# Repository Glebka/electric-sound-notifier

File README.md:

# Electric Sound Notifier

Device designed to be connected to an AC-DC USB charger adapter. Upon plugging in, it emits three beeps to signal the presence of mains voltage. When the mains voltage is no longer detected it produces a prolonged beep.

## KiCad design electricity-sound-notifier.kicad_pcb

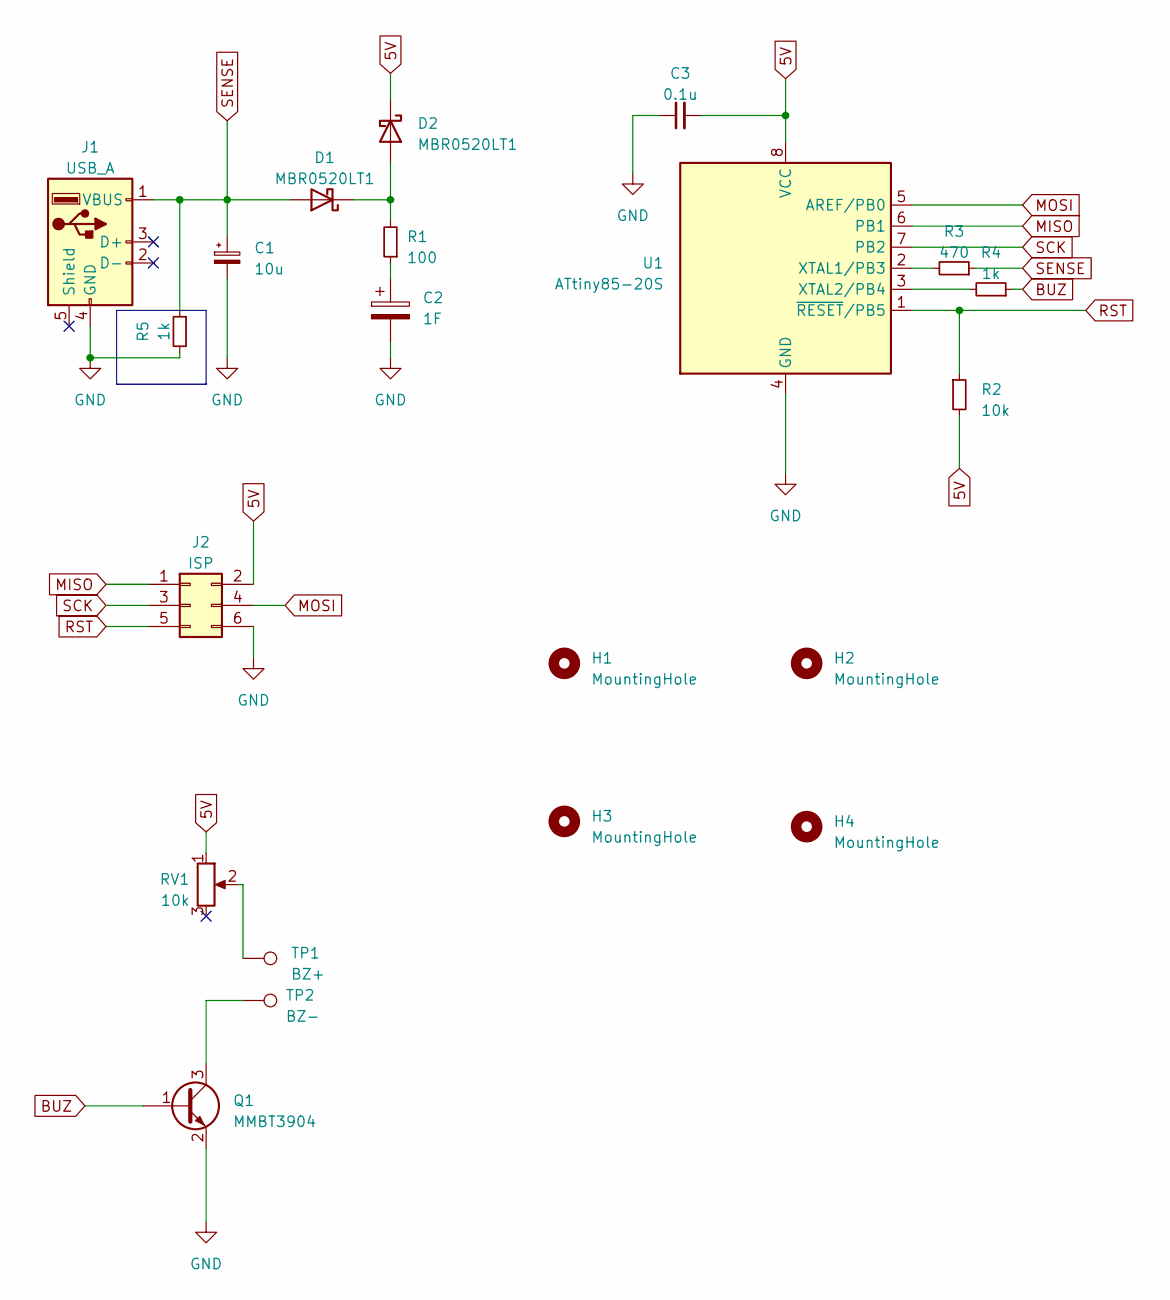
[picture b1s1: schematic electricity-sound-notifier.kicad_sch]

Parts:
C1: 10u; CP_EIA-3216-10_Kemet-I_Pad1.58x1.35mm_HandSolder
C2: 1F; KAMCAP-5R5-D105VYC3H
C3: 0.1u; C_0603_1608Metric
D1, D2: MBR0520LT1; D_SOD-123
H1, H2, H3, H4: MountingHole; MountingHole_2.5mm
J1: USB_A; USB_A_CNCTech_1001-011-01101_Horizontal
J2: ISP; PinHeader_2x03_P2.54mm_Vertical
Q1: MMBT3904; SOT-23
R1: 100; R_0603_1608Metric
R2: 10k; R_0603_1608Metric
R3: 470; R_0603_1608Metric
R4, R5: 1k; R_0603_1608Metric
RV1: 10k; Potentiometer_Runtron_RM-065_Vertical
TP1: BZ+; TestPoint_Pad_1.5x1.5mm
TP2: BZ-; TestPoint_Pad_1.5x1.5mm
U1: ATtiny85-20S; SOIC-8W_5.3x5.3mm_P1.27mm

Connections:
5V: C3.2, D2.1 (K), J2.2, R2.2, RV1.1, U1.8 (VCC)
BUZ: Q1.1 (B), R4.1
GND: C1.2, C2.2, C3.1, J1.4 (GND), J2.6, Q1.2 (E), R5.2, U1.4 (GND)
MISO: J2.1, U1.6 (PB1)
MOSI: J2.4, U1.5 (AREF/PB0)
unnamed: C2.1, R1.1
unnamed: D1.1 (K), D2.2 (A), R1.2
unnamed: Q1.3 (C), TP2.1
unnamed: RV1.2, TP1.1
unnamed: R3.2, U1.2 (XTAL1/PB3)
unnamed: R4.2, U1.3 (XTAL2/PB4)
RST: J2.5, R2.1, U1.1 (~RESET/PB5)
SCK: J2.3, U1.7 (PB2)
SENSE: C1.1, D1.2 (A), J1.1 (VBUS), R3.1, R5.1

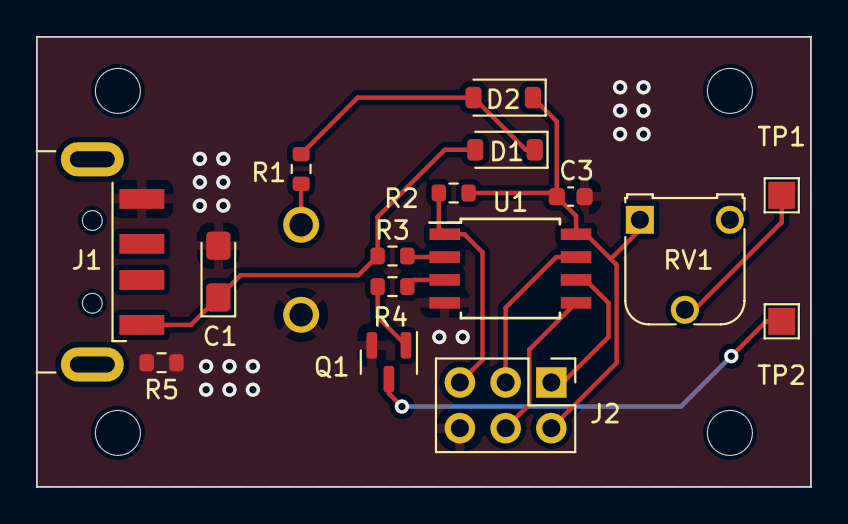
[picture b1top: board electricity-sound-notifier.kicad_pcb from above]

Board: 2 copper layers, 43.0 x 25.0 mm, 21 parts (1 on the bottom side), 14 nets.
